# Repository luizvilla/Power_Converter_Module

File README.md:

# Power_Converter_Module
This repository holds an open-hardware Power Converter Module

Copyright LAAS 2016

This documentation describes Open Hardware and is licensed under the
CERN OHL v. 1.2.

You may redistribute and modify this documentation under the terms of the
CERN OHL v.1.2. (http://ohwr.org/cernohl). This documentation is distributed
WITHOUT ANY EXPRESS OR IMPLIED WARRANTY, INCLUDING OF
MERCHANTABILITY, SATISFACTORY QUALITY AND FITNESS FOR A
PARTICULAR PURPOSE. Please see the CERN OHL v.1.2 for applicable
conditions

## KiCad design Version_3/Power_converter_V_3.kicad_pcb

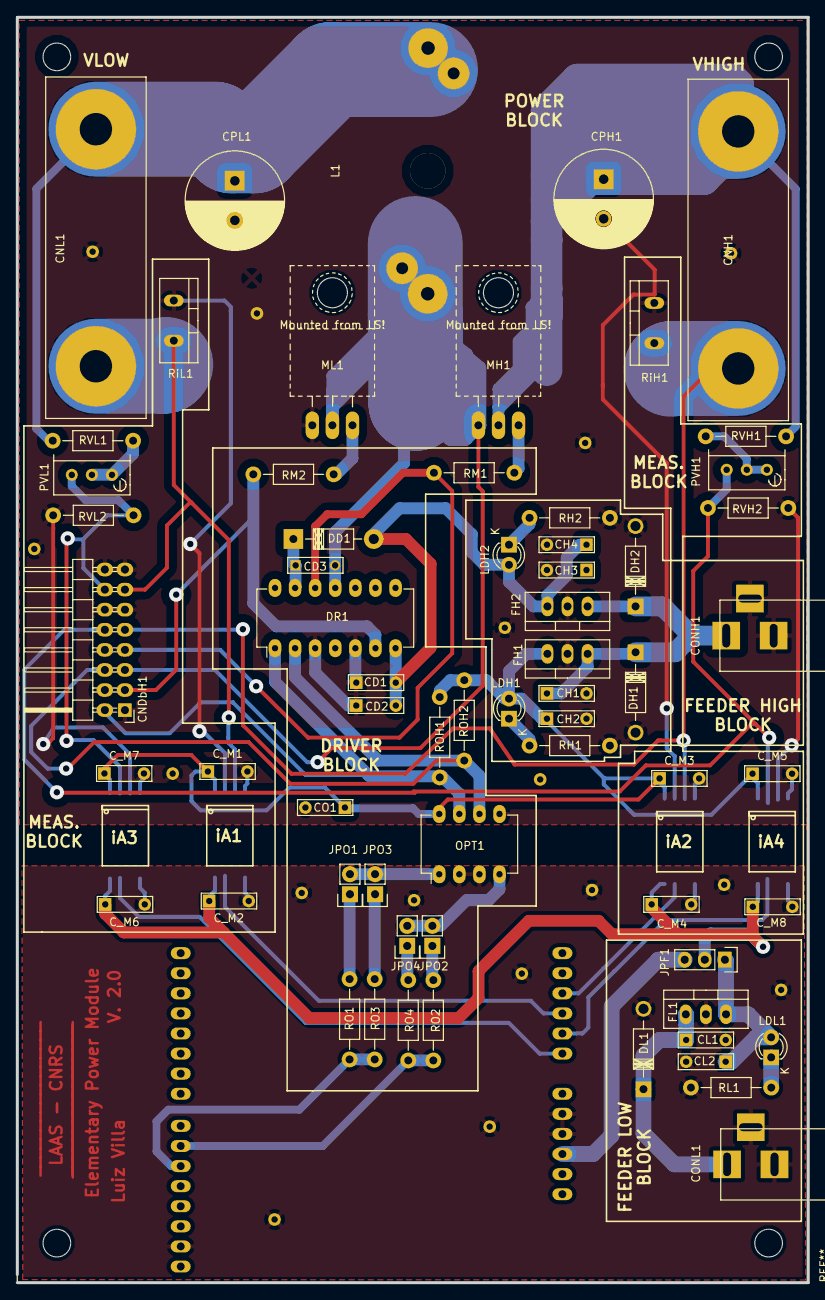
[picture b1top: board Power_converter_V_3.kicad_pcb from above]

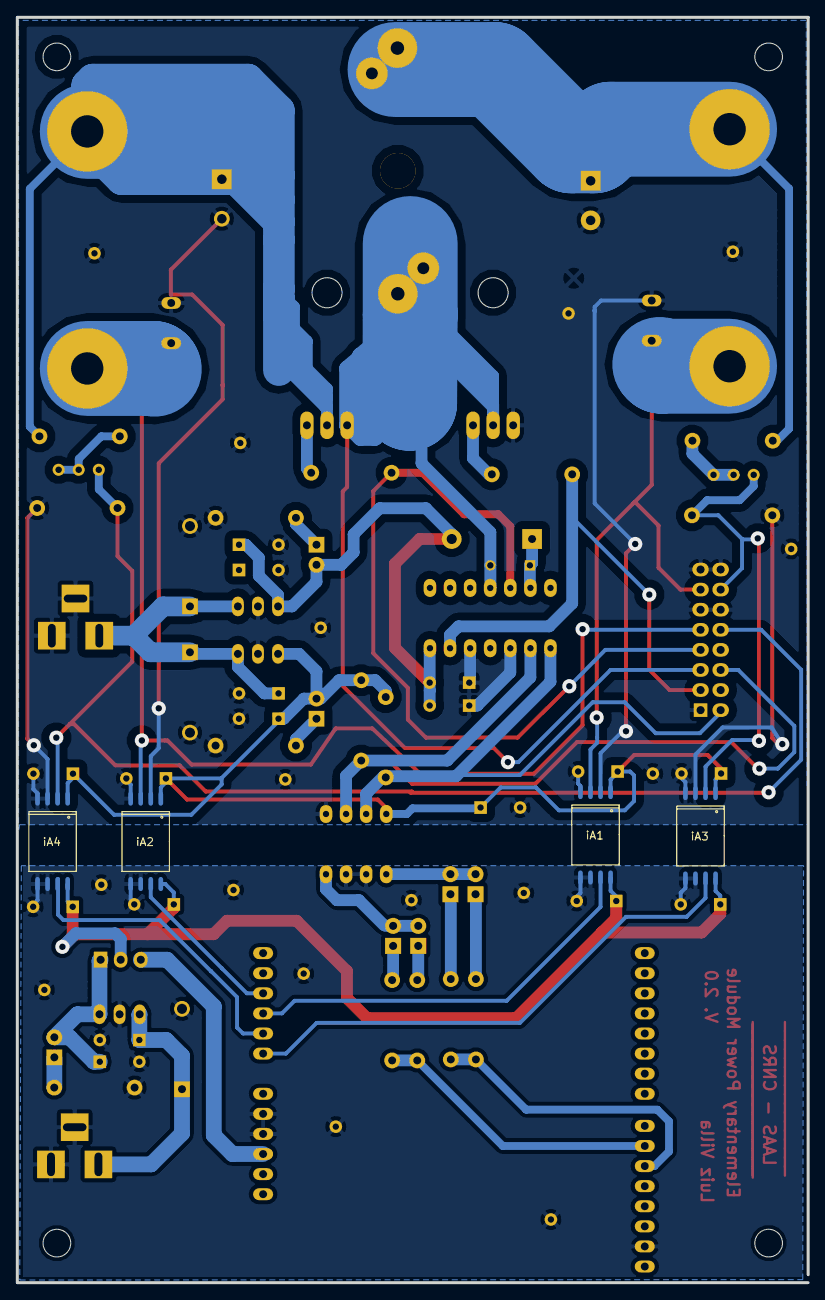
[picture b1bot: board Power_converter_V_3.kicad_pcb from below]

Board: 2 copper layers, 100.0 x 160.0 mm, 69 parts (4 on the bottom side), 40 nets.

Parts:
CD1, CD2: 100n; C_Rect_L7_W2_P5_fat
CD3: 500n; C_Rect_L7_W2_P5
CH1, CH2, CH3, CH4: 1u; C_Rect_L7_W2_P5_fat
CL1, CL2: 1u; C_Rect_L7_W2_P5_fat
CNDbH1: CONN_02X08; Pin_Header_Angled_2x08_large
CNH1: HIGH; Banana_Jack_2Pin
CNL1: LOW; Banana_Jack_2Pin
CO1: C; C_Rect_L7_W2_P5_fat
CONH1: BARREL_JACK
CONL1: BARREL_JACK
CPH1: C; C_Radial_D12.5_L25_P5
CPL1: C; C_Radial_D12.5_L25_P5
C_M1, C_M2, C_M3, C_M4, C_M5, C_M6, C_M7, C_M8: 100nF; C_Rect_L7_W2_P5_fat
DD1: DIODE; Diode_DO-41_SOD81_Horizontal_RM10
DH1, DH2: D_Small; Diode_DO-41_SOD81_Horizontal_RM10
DL1: D_Small; Diode_DO-41_SOD81_Horizontal_RM10
DR1: IRS2186; DIP-14_W7.62mm_LongPads
FH1: 7805
FH2: 7815; 7805
FL1: 7805
JPF1: JUMPER3; Pin_Header_Straight_1x03
JPO1, JPO2, JPO3, JPO4: JUMPER; Pin_Header_Straight_1x02
L1: INDUCTOR; MURATA_Inductor_Big
LDH1, LDH2: LED; LED-3MM
LDL1: LED; LED-3MM
MH1: FDPF39N20; TO-220_Neutral123_Horizontal_MountedFromLS_LargePads
ML1: FDPF39N20; TO-220_Neutral123_Horizontal_MountedFromLS_LargePads
OPT1: TLP2631; DIP-8_W7.62mm_LongPads
PVH1: 1M; Potentiometer_Bourns_3296W_3-8Zoll_Inline_ScrewUp
PVL1: 1M; Potentiometer_Bourns_3296W_3-8Zoll_Inline_ScrewUp
RH1, RH2: 10k; Resistor_Horizontal_RM10mm
RL1: 10k; Resistor_Horizontal_RM10mm
RM1, RM2: 2R2; Resistor_Horizontal_RM10mm
RO1, RO2: 470; Resistor_Horizontal_RM10mm
RO3, RO4: 220; Resistor_Horizontal_RM10mm
ROH1, ROH2: R; Resistor_Horizontal_RM10mm
RVH1: 470k; Resistor_Horizontal_RM10mm
RVH2: 4k7; Resistor_Horizontal_RM10mm
RVL1: 470k; Resistor_Horizontal_RM10mm
RVL2: 4k7; Resistor_Horizontal_RM10mm
RiH1: 0.02; Resistor_TO-220_Vertical
RiL1: 0.02; Resistor_TO-220_Vertical
SH_1: ARDUINO_SHIELD; ARDUINO_SHIELD_2
iA1, iA2, iA3, iA4: AMC1100

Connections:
/Driver Block/+5VHigh: CH2.1, CO1.1, C_M1.1, C_M3.1, C_M5.1, C_M7.1, FH1.VO, LDH1.2, OPT1.8, ROH1.1, ROH2.1, iA1.1, iA2.1, iA3.1, iA4.1
/Driver Block/+15VHigh: CD1.2, CD2.2, CH4.1, DD1.2, DR1.7, FH2.VO, LDH2.2
/Driver Block/Hin: CNDbH1.2, DR1.1, OPT1.7, ROH1.2
/Driver Block/Lin: CNDbH1.6, DR1.2, OPT1.6, ROH2.2
/Driver Block/PWMH1: RO1.1, RO3.1, SH_1.10
/Driver Block/PWML1: RO2.1, RO4.1, SH_1.9
/Driver Block/VgH: CNDbH1.7, DR1.12, RM1.2
/Driver Block/VgL: CNDbH1.3, DR1.6, RM2.1
/Driver Block/VsH: CD3.2, CNDbH1.5, DR1.11, L1.1, MH1.3, ML1.2
/Feeder Block/+5VAd: JPF1.3, SH_1.5V
/Feeder Block/+5VLow: C_M2.1, C_M4.1, C_M6.1, C_M8.1, JPF1.2, iA1.8, iA2.8, iA3.8, iA4.8
/Feeder Block/Vhigh: CNH1.1, CPH1.1, MH1.2, RVH1.2
/Feeder Block/Vlow: CNL1.1, CPL1.1, L1.2, RVL1.2
/Measurement Block/VH+: CNDbH1.10, PVH1.3, RVH2.2, iA4.2
/Measurement Block/VL+: CNDbH1.14, PVL1.3, RVL2.2, iA3.2
/Measurement Block/ViH-: CNDbH1.9, CNH1.2, RiH1.1, iA2.3
/Measurement Block/ViL-: CNDbH1.13, CNL1.2, RiL1.2, iA1.3
/Measurement Block/VmVH+: SH_1.AD1, iA4.7
/Measurement Block/VmVL+: SH_1.AD0, iA3.7
/Measurement Block/VmiH+: SH_1.AD3, iA2.7
/Measurement Block/VmiL+: SH_1.AD2, iA1.7
/debug_block/GNDVHigh: CNDbH1.4, CNDbH1.8
GND: CD1.1, CD2.1, CH1.2, CH2.2, CH3.2, CH4.2, CL1.2, CL2.2, CNDbH1.1, CNDbH1.11, CNDbH1.12, CNDbH1.15, CNDbH1.16, CO1.2, CONH1.2, CONH1.3, CONL1.2, CONL1.3, CPH1.2, CPL1.2, C_M1.2, C_M2.2, C_M3.2, C_M4.2, C_M5.2, C_M6.2, C_M7.2, C_M8.2, DH1.2, DH2.2, DL1.2, DR1.3, DR1.5, FH1.GND, FH2.GND, FL1.GND, ML1.3, OPT1.2, OPT1.3, OPT1.5, RH1.2, RH2.2, RL1.2, RVH2.1, RVL2.1, RiH1.2, RiL1.1, SH_1.GND1, SH_1.GND2, SH_1.GND3, iA1.2, iA1.4, iA1.5, iA1.6, iA2.2, iA2.4, iA2.5, iA2.6, iA3.3, iA3.4, iA3.5, iA3.6, iA4.3, iA4.4, iA4.5, iA4.6
unnamed: CD3.1, DD1.1, DR1.13
unnamed: CH1.1, CH3.1, CONH1.1, DH1.1, DH2.1, FH1.VI, FH2.VI
unnamed: CL1.1, CONL1.1, DL1.1, FL1.VI
unnamed: CL2.1, FL1.VO, JPF1.1, LDL1.2
unnamed: JPO1.1, RO1.2
unnamed: JPO1.2, JPO3.2, OPT1.1
unnamed: JPO2.1, RO2.2
unnamed: JPO2.2, JPO4.2, OPT1.4
unnamed: JPO3.1, RO3.2
unnamed: JPO4.1, RO4.2
unnamed: LDH1.1, RH1.1
unnamed: LDH2.1, RH2.1
unnamed: LDL1.1, RL1.1
unnamed: MH1.1, RM1.1
unnamed: ML1.1, RM2.2
unnamed: PVH1.1, PVH1.2, RVH1.1
unnamed: PVL1.1, PVL1.2, RVL1.1

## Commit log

2017-03-07 This is the current version of the hardware files
2017-04-06 The construction manual for the Power Converter
    This is the constrution manual. It still has errors, but it is a start. The licence needs to be changed still.
